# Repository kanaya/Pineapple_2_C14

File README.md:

Pineapple_2_C14
===============

Pineapple II C14

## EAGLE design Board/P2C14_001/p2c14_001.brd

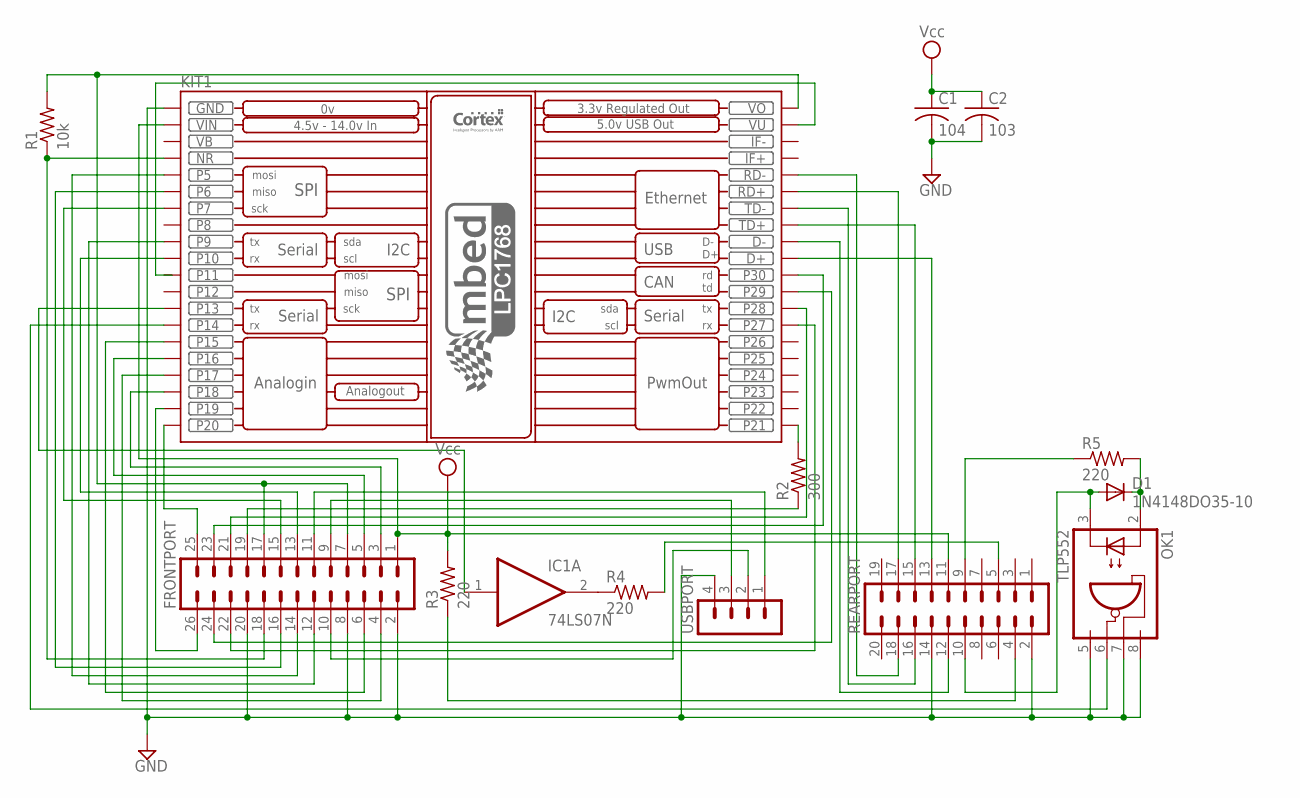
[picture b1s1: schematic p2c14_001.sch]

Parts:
C1: 104; C025-025X050
C2: 103; C050-075X075
D1: 1N4148DO35-10; DO35-10
FRONTPORT: ML26L
IC1: 74LS07N; DIL14
KIT1: MBED_NXP_LPC1768; MBED-KIT
OK1: TLP552; DIL08
R1: 10k; 0204/7
R2: 300; 0204/7
R3, R4, R5: 220; 0204/7
REARPORT: ML20L
USBPORT: MA04-1

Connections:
GND: C1.2, C2.2, FRONTPORT.2, FRONTPORT.8, FRONTPORT.20, IC1.7 (GND), KIT1.GND, OK1.5 (GND), OK1.7 (VE), OK1.8 (VCC), REARPORT.2, REARPORT.14, USBPORT.4
unnamed: R3.1, REARPORT.4
unnamed: IC1.2 (O), R4.1
unnamed: D1.C, OK1.2 (A), R5.2
unnamed: R5.1, REARPORT.9
unnamed: KIT1.P$14 (P14), OK1.6 (VO)
unnamed: KIT1.D-, REARPORT.12
unnamed: D1.A, OK1.3 (C), REARPORT.10
unnamed: KIT1.D+, REARPORT.13
unnamed: FRONTPORT.18, KIT1.NR, R1.1
unnamed: FRONTPORT.12, KIT1.P$9 (P9)
unnamed: FRONTPORT.11, USBPORT.1
unnamed: FRONTPORT.3, KIT1.P$18 (P18)
unnamed: FRONTPORT.4, KIT1.P$17 (P17)
unnamed: FRONTPORT.5, KIT1.P$16 (P16)
unnamed: FRONTPORT.6, KIT1.P$15 (P15)
unnamed: KIT1.P$21 (P21), R2.2
unnamed: KIT1.TD+, REARPORT.15
unnamed: FRONTPORT.13, KIT1.P$10 (P10)
unnamed: FRONTPORT.14, KIT1.P$5 (P5)
unnamed: FRONTPORT.15, KIT1.P$7 (P7)
unnamed: FRONTPORT.16, KIT1.P$6 (P6)
unnamed: FRONTPORT.19, R2.1
unnamed: FRONTPORT.21, KIT1.P$28 (P28)
unnamed: FRONTPORT.22, KIT1.P$27 (P27)
unnamed: FRONTPORT.23, KIT1.P$30 (P30)
unnamed: FRONTPORT.24, KIT1.P$29 (P29)
unnamed: FRONTPORT.25, KIT1.P$20 (P20)
unnamed: FRONTPORT.26, KIT1.P$19 (P19)
unnamed: IC1.1 (I), KIT1.P$13 (P13)
unnamed: R4.2, REARPORT.5
unnamed: KIT1.TD-, REARPORT.16
unnamed: KIT1.RD+, REARPORT.17
unnamed: KIT1.RD-, REARPORT.18
unnamed: FRONTPORT.7, FRONTPORT.17, KIT1.VOUT (VO), R1.2
unnamed: FRONTPORT.10, USBPORT.2
unnamed: FRONTPORT.9, USBPORT.3
VB: KIT1.VB
VCC: C1.1, C2.1, FRONTPORT.1, IC1.14 (VCC), KIT1.VIN, R3.2, REARPORT.11

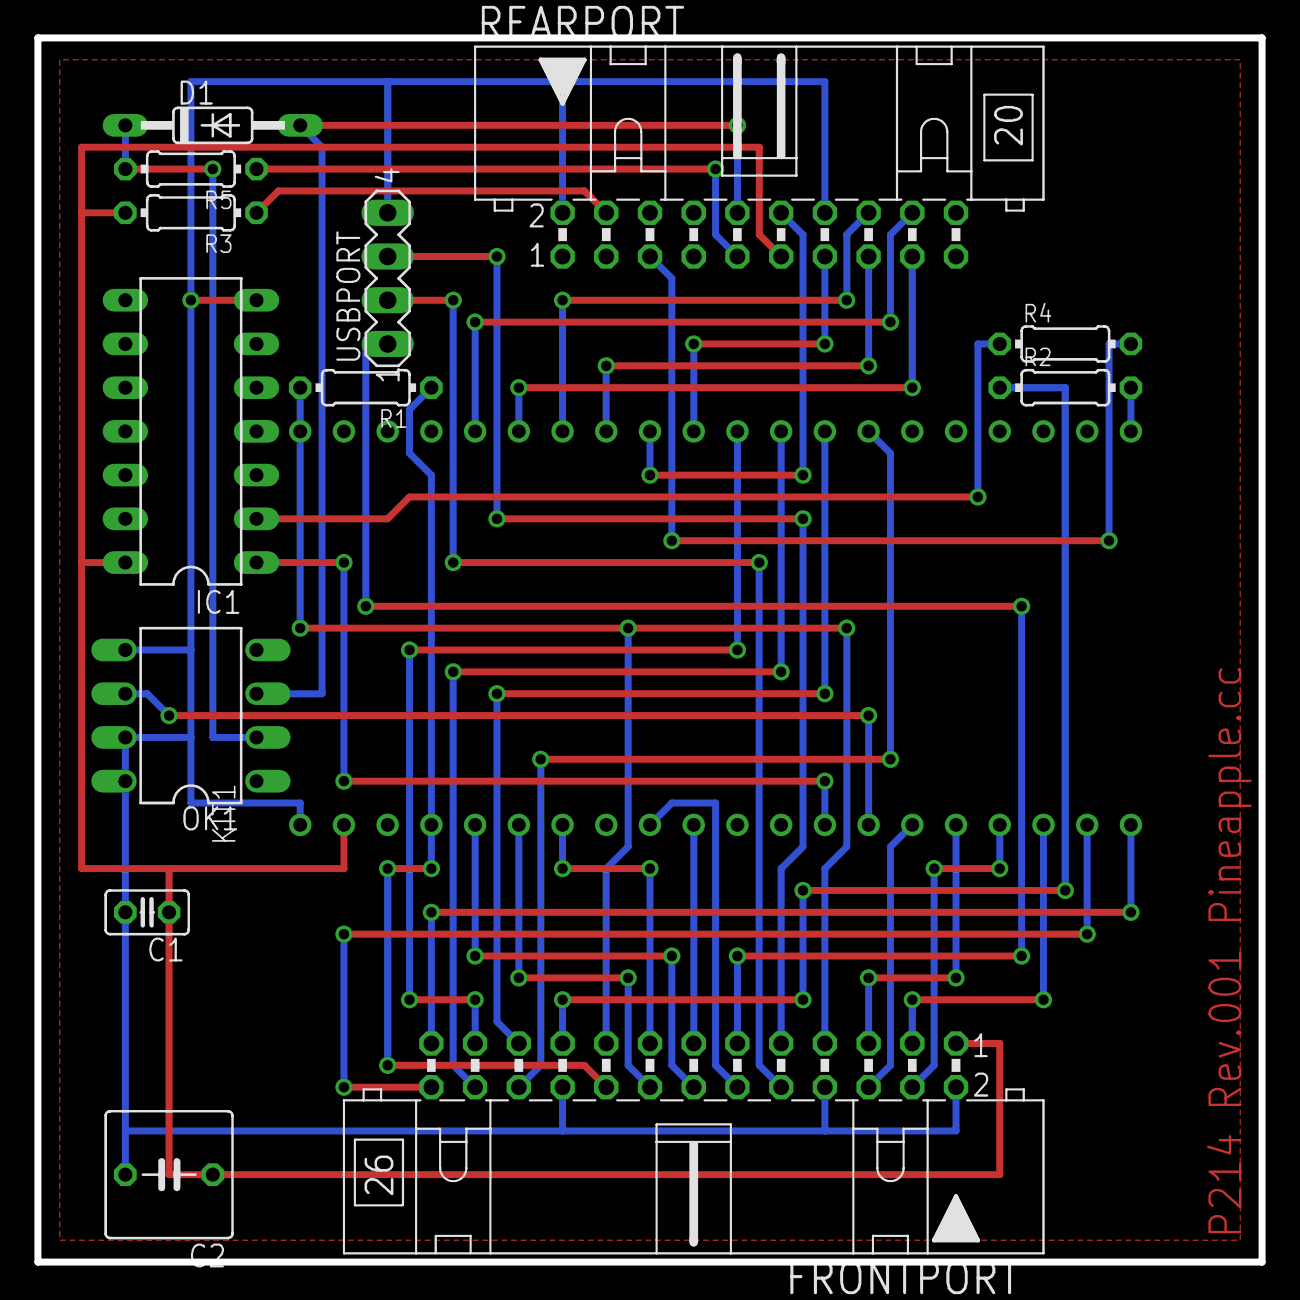
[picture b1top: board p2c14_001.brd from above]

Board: 2 copper layers, 71.1 x 71.1 mm, 14 parts (0 on the bottom side), 38 nets.

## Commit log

2014-04-29 Initial commit.
